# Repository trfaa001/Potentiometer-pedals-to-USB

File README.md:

# DIY USB Game Pedals with Arduino & Logitech G29 Wiring

This project turns **three potentiometers** into fully functional USB game pedals (clutch, brake, accelerator) using an Arduino and the [Arduino Joystick Library](https://github.com/MHeironimus/ArduinoJoystickLibrary).

---

## Features

- **3 Analog Pedals** mapped to USB joystick axes:
  - **Rx** → Pedal 1 (e.g., Clutch)
  - **Ry** → Pedal 2 (e.g., Brake)
  - **Rz** → Pedal 3 (e.g., Accelerator)
- **Gaussian smoothing filter** to reduce noise and jitter
- **Automatic min/max calibration** at startup and during use
- **Compatible with Logitech G29 pedal wiring** (KiCad schematic included)
- **Plug-and-play USB HID device**

---

## Hardware Requirements

- **Arduino Leonardo**, Micro, or any Arduino board with native USB HID support (only tested on Leonardo)  
  *(Uno/Nano will not work without extra firmware flashing)*
- **3x potentiometers** (e.g., from Logitech G29 pedals)
- **Wiring** (Dupont cables or soldered connections)
- *(Optional)* Capacitors for physical low-pass filter.

---

## Wiring

The potentiometers are connected to the Arduino’s analog pins:

| Pedal   | Arduino Pin |
|---------|-------------|
| Pedal 1 | A0          |
| Pedal 2 | A1          |
| Pedal 3 | A2          |

Each potentiometer also connects to **5V** and **GND**.

If using Logitech G29 pedals, refer to the included [**KiCad schematic**](/hardware/kicad/g29pedals/schematic.jpg) for the correct pinout.

---

## Software Setup

1. **Install Arduino IDE**
2. **Install Joystick Library**  
   - Open Arduino IDE → Sketch → Include Library → Manage Libraries  
   - Search for `Joystick` by Matthew Heironimus and install
3. **Select Board**  
   - Tools → Board → Arduino Leonardo (or compatible)
4. **Upload the Code**  
   - Flash the provided `.ino` file to your Arduino

---

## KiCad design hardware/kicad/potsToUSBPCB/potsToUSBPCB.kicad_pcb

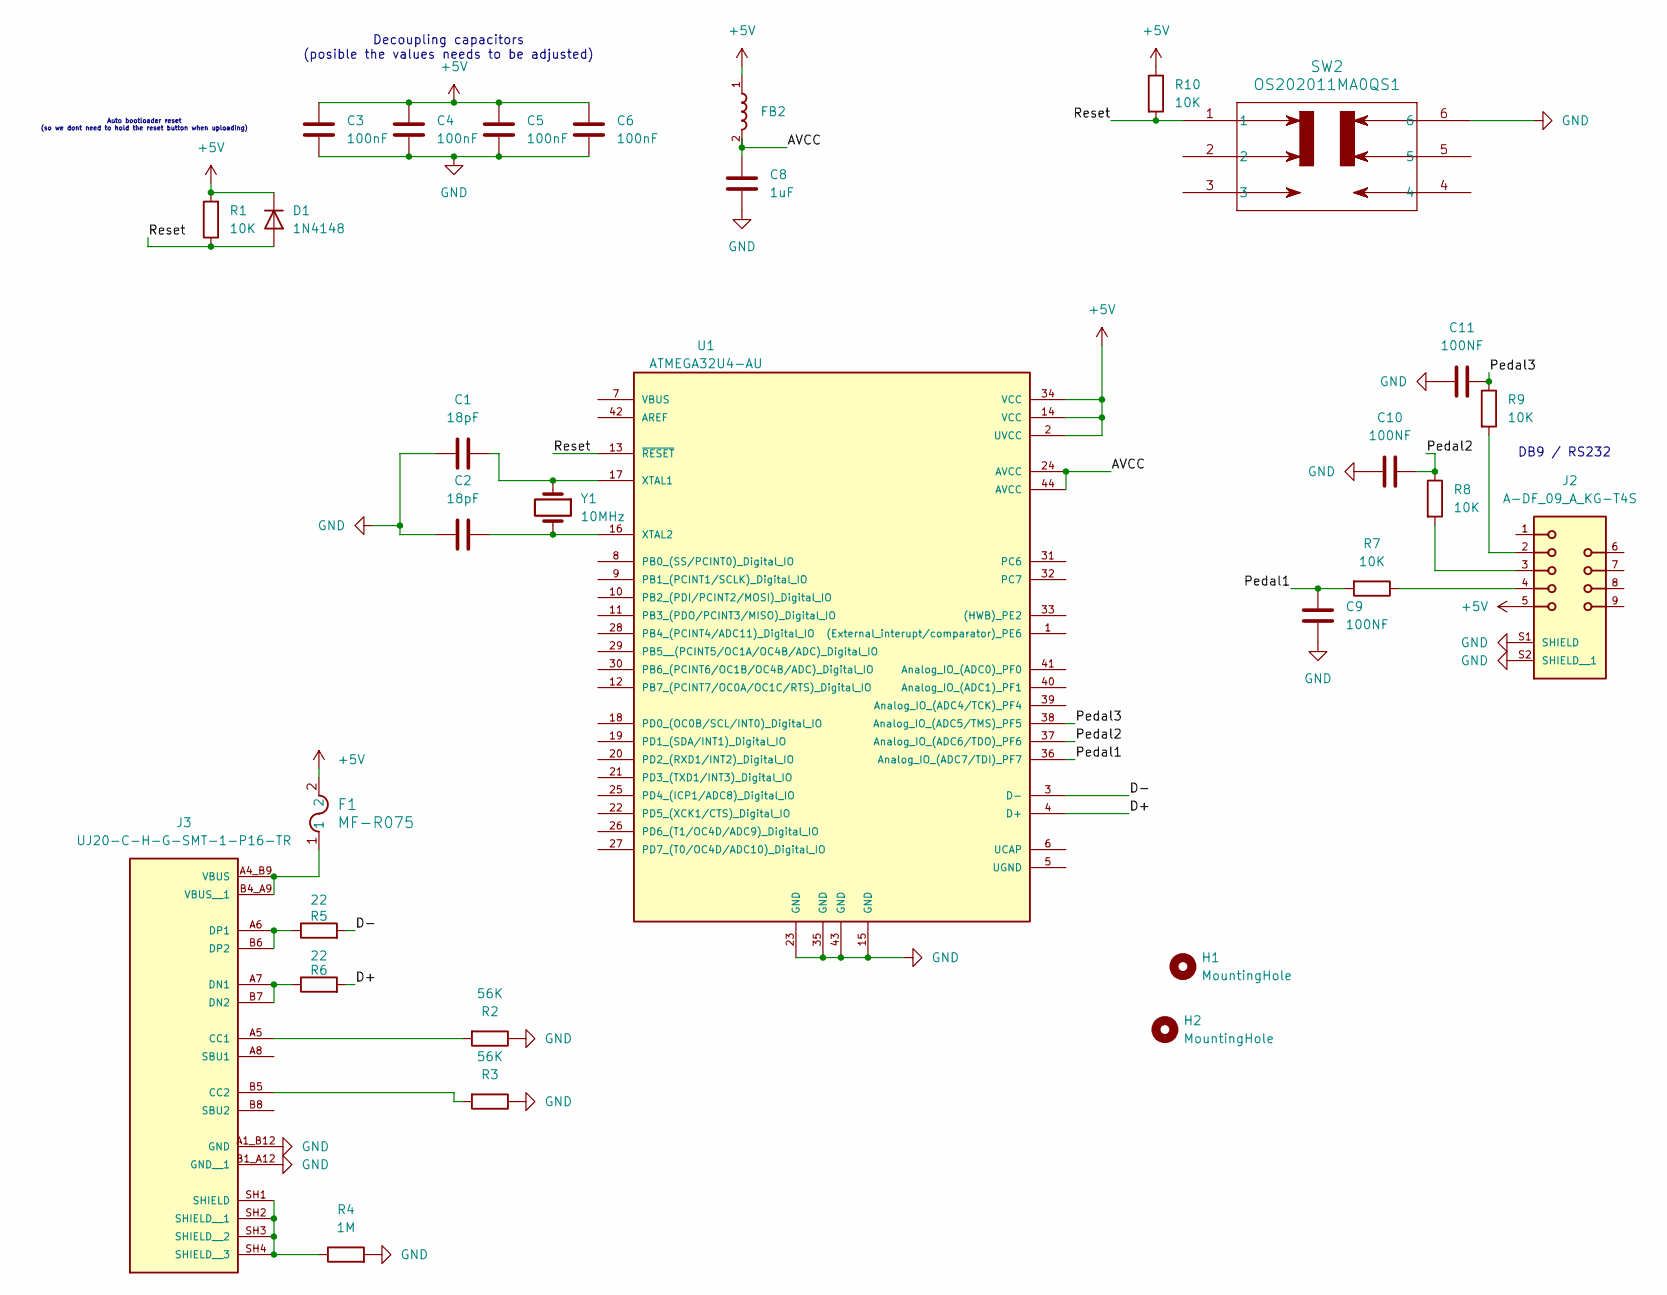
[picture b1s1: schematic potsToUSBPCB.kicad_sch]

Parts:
C1, C2: 18pF; C_Disc_D5.0mm_W2.5mm_P5.00mm
C3, C4, C5, C6: 100nF; C_0805_2012Metric_Pad1.18x1.45mm_HandSolder
C8: 1uF; L_1206_3216Metric_Pad1.42x1.75mm_HandSolder
C9, C10, C11: 100NF; C_0805_2012Metric_Pad1.18x1.45mm_HandSolder
D1: 1N4148; Nexperia_CFP3_SOD-123W
F1: MF-R075; FUS_MF-R075_BRN
FB2: 30R 3A; IND_BOURNS_MH2029; MPN MH2029-300Y
H1, H2: MountingHole; MountingHole_2.2mm_M2
J2: A-DF_09_A_KG-T4S; ASSMANN_A-DF_09_A_KG-T4S; PARTREV 05
J3: UJ20-C-H-G-SMT-1-P16-TR; SAMESKY_UJ20-C-H-G-SMT-1-P16-TR; PARTREV 1.0
R1, R7, R8, R9, R10: 10K; R_1206_3216Metric_Pad1.30x1.75mm_HandSolder
R2, R3: 56K; R_1206_3216Metric_Pad1.30x1.75mm_HandSolder
R4: 1M; R_1206_3216Metric_Pad1.30x1.75mm_HandSolder
R5, R6: 22; R_1206_3216Metric_Pad1.30x1.75mm_HandSolder
SW2: OS202011MA0QS1; SW6_OS202011MA0QS1_CNK
U1: ATMEGA32U4-AU; TQFP-44-1EP_10x10mm_P0.8mm_EP4.5x4.5mm
Y1: 10MHz; XTAL_ABLS2-8.000MHZ-D4Y-T

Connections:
+5V: C3.1, C4.1, C5.1, C6.1, D1.1 (K), F1.2, FB2.1, J2.5, R1.2, R10.1, U1.2 (UVCC), U1.14 (VCC), U1.34 (VCC)
/AVCC: C8.1, FB2.2, U1.24 (AVCC), U1.44 (AVCC)
/D+: R6.2, U1.4 (D+)
/D-: R5.2, U1.3 (D-)
/Pedal1: C9.1, R7.2, U1.36 (Analog_IO_(ADC7/TDI)_PF7)
/Pedal2: C10.1, R8.1, U1.37 (Analog_IO_(ADC6/TDO)_PF6)
/Pedal3: C11.1, R9.1, U1.38 (Analog_IO_(ADC5/TMS)_PF5)
/Reset: D1.2 (A), R1.1, R10.2, SW2.1, U1.13 (~RESET)
GND: C1.2, C2.1, C3.2, C4.2, C5.2, C6.2, C8.2, C9.2, C10.2, C11.2, J2.S1 (SHIELD), J2.S2 (SHIELD__1), J3.A1_B12 (GND), J3.B1_A12 (GND__1), R2.1, R3.1, R4.2, SW2.6, U1.15 (GND), U1.23 (GND), U1.35 (GND), U1.43 (GND)
unnamed: J2.2, R9.2
unnamed: J2.3, R8.2
unnamed: J2.4, R7.1
unnamed: J3.A5 (CC1), R2.2
unnamed: J3.B5 (CC2), R3.2
unnamed: J3.A7 (DN1), J3.B7 (DN2), R6.1
unnamed: J3.A6 (DP1), J3.B6 (DP2), R5.1
unnamed: J3.SH1 (SHIELD), J3.SH2 (SHIELD__1), J3.SH3 (SHIELD__2), J3.SH4 (SHIELD__3), R4.1
unnamed: F1.1, J3.A4_B9 (VBUS), J3.B4_A9 (VBUS__1)
unnamed: C1.1, U1.17 (XTAL1), Y1.1
unnamed: C2.2, U1.16 (XTAL2), Y1.2

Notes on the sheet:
Decoupling capacitors (posible the values needs to be adjusted)
DB9 / RS232
Auto bootloader reset (so we dont need to hold the reset button when uploading)

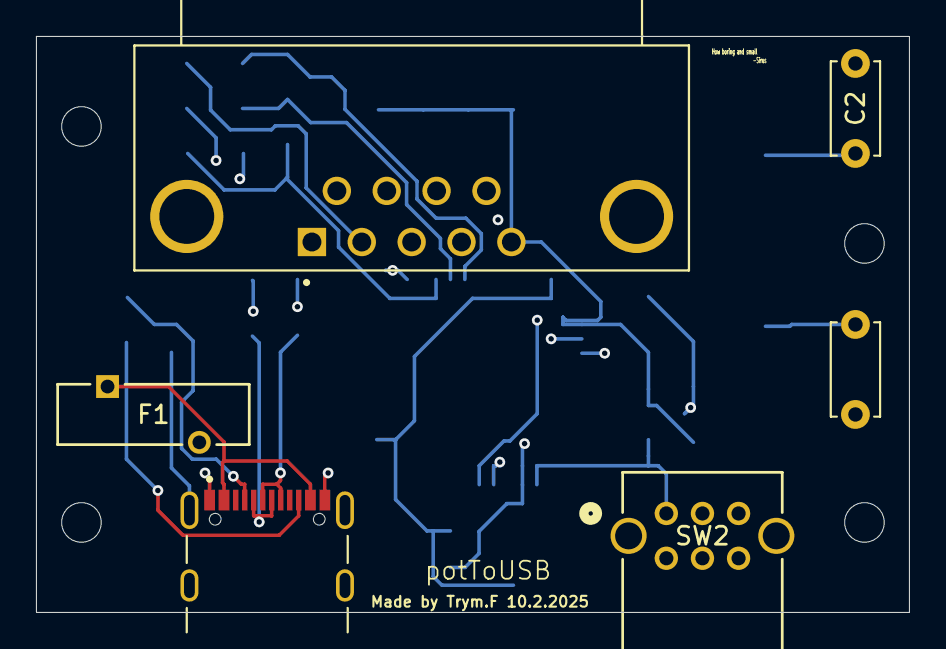
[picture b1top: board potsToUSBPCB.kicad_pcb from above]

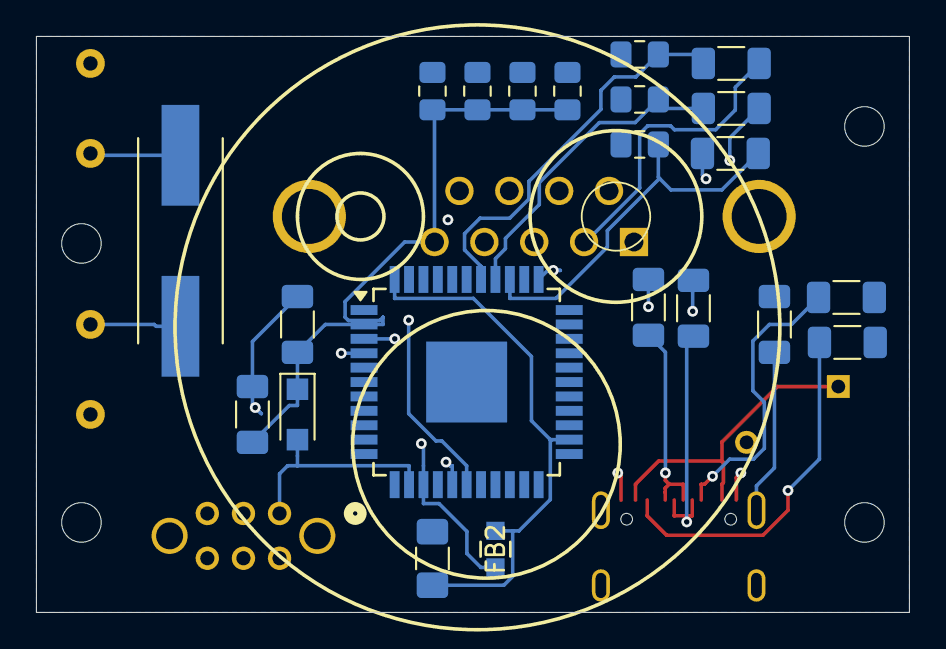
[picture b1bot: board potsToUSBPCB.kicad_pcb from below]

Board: 4 copper layers, 48.5 x 32.0 mm, 32 parts (22 on the bottom side), 20 nets.

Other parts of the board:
H3, H4: MountingHole; MountingHole_2.2mm_M2

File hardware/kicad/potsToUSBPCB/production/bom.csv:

Designator,Footprint,Quantity,Value,LCSC Part #
"C1, C2",C_Disc_D5.0mm_W2.5mm_P5.00mm,2,18pF,
"C10, C11, C3, C4, C5, C6, C9",0805,7,100NF,
C8,1206,1,1uF,
D1,Nexperia_CFP3_SOD-123W,1,1N4148,
F1,FUS_MF-R075_BRN,1,MF-R075,
FB2,IND_BOURNS_MH2029,1,30R 3A,MH2029-300Y
J2,ASSMANN_A-DF_09_A_KG-T4S,1,A-DF_09_A_KG-T4S,
J3,SAMESKY_UJ20-C-H-G-SMT-1-P16-TR,1,UJ20-C-H-G-SMT-1-P16-TR,
"R1, R10, R7, R8, R9",1206,5,10K,
"R2, R3",1206,2,56K,
R4,1206,1,1M,
"R5, R6",1206,2,22,
SW2,SW6_OS202011MA0QS1_CNK,1,OS202011MA0QS1,
U1,TQFP-44-1EP_10x10mm_P0.8mm_EP4.5x4.5mm,1,ATMEGA32U4-AU,
Y1,XTAL_ABLS2-8.000MHZ-D4Y-T,1,10MHz,

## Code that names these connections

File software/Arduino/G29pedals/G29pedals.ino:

#include <Joystick.h>



Joystick_ Joystick(JOYSTICK_DEFAULT_REPORT_ID,JOYSTICK_TYPE_GAMEPAD,
  0, 0,                    // Button Count, Hat Switch Count
  false, false, false,     // No x, Y or Z
  true, true, true,        // Rx, Ry, or Rz
  false, false,            // No rudder or throttle
  false, false, false);    // No accelerator, brake, or steering

// Define IO pins
const int pedal1 = A0;
const int pedal2 = A1;
const int pedal3 = A2;

// Start values for Min and Max values
int pedal1Max = 100;
int pedal1Min = 0;

int pedal2Max = 100;
int pedal2Min = 0;

int pedal3Max = 100;
int pedal3Min = 0;

// Time keeping
unsigned long calibrationStart;
unsigned long timeLastMaxCalibration;

// Variables for logic
unsigned long analogReadings; // Variable to store readings that add up to one big number

int amountOfReadings; // Variable to store the amount of analog readings taken

float dataPedal1[5]; // A collection of the most recent reading from pedal1
float dataPedal2[5]; // A collection of the most recent reading from pedal2
float dataPedal3[5]; // A collection of the most recent reading from pedal3

float kernel[5]; // The kernel for pedal1

float filterOutputPedal1[5]; // The output of the filter from pedal 1
float filterOutputPedal2[5]; // The output of the filter from pedal 2
float filterOutputPedal3[5]; // The output of the filter from pedal 3

float kernelSum = 0; 

// Constant variables for logic
const int amountOfReadingsForMax = 10;
const int millisForMinCalibration = 1000; // The time for taking the average of the "minimum" value of each pedal
const unsigned long timeBetweenMaxCalibration = 5; // The time between checking if there is a new max

const int kernelSize = 5; // Variables for Guassian kernel
const float sigma = 2.0; // Standard deviation

void setup() {
  // Define pin modes
  pinMode(pedal1, INPUT);
  pinMode(pedal2, INPUT);
  pinMode(pedal3, INPUT);

  gaussianKernel(); // Calculates the gaussian kernel

  // Calibrate the minimum of the pedals
  pedal1Min = minCalibration(pedal1);
  pedal2Min = minCalibration(pedal2);
  pedal3Min = minCalibration(pedal3);

  Joystick.begin(); // Begin the joystick library

  setCalibrationForAxis();

  Serial.begin(9600);


}

void loop() {

  // If enough time has passed check if the pedals can reach a higher value
  if ((millis() - timeLastMaxCalibration) > timeBetweenMaxCalibration){
      pedal1Max = maxCalibration(1, pedal1Max);
      pedal2Max = maxCalibration(2, pedal2Max);
      pedal3Max = maxCalibration(3, pedal3Max);
      setCalibrationForAxis();

      timeLastMaxCalibration = millis();
  }

  takeInputs();
  calculateOutput();

  Joystick.setRxAxis(filterOutputPedal1[kernelSize-1]);
  Joystick.setRyAxis(filterOutputPedal2[kernelSize-1]);
  Joystick.setRzAxis(filterOutputPedal3[kernelSize-1]);

}

void setCalibrationForAxis(){
  // Sets the range for the pedals

  Joystick.setRxAxisRange(pedal1Min, pedal1Max);
  Joystick.setRyAxisRange(pedal2Min, pedal2Max);
  Joystick.setRzAxisRange(pedal3Min, pedal3Max);
}

int minCalibration(int analogPin){
  // Reset the variables so the function can be used multiple times
  analogReadings = 0;
  amountOfReadings = 0;
  calibrationStart = millis();

  //Take the average of all the reading in a second and return it (asume the user doesnt touch the pedals the first 3 seconds)
  while ((millis() - calibrationStart) < millisForMinCalibration){
    analogReadings += analogRead(analogPin);
    amountOfReadings += 1;

  }

  return analogReadings / amountOfReadings;
}

int maxCalibration(int pedal, int pedalMax){
  // Reset the variables so the function can be used multiple times
  analogReadings = 0;
  amountOfReadings = amountOfReadingsForMax;

  if (pedal == 1){
    for (int i = 0; i < amountOfReadingsForMax; i++){ //We are only doing 10 readings to save on proccesing time
      analogReadings += filterOutputPedal1[kernelSize-1];
    }
  }
  else if (pedal == 2){
    for (int i = 0; i < amountOfReadingsForMax; i++){ //We are only doing 10 readings to save on proccesing time
      analogReadings += filterOutputPedal2[kernelSize-1];
    }
  }
  else if (pedal == 3){
    for (int i = 0; i < amountOfReadingsForMax; i++){ //We are only doing 10 readings to save on proccesing time
      analogReadings += filterOutputPedal3[kernelSize-1];
    }
  }


  if ((analogReadings / amountOfReadingsForMax) > pedalMax){
    
    return analogReadings / amountOfReadingsForMax;
  }
  else{
    return pedalMax;
  }

    
}

void takeInputs(){
  // Moves the data in the data array one point forward, registering the input and saving the 4 previous ones for later use

  for (int i = 0; i < kernelSize; i++){
    if (i == kernelSize - 1){
      dataPedal1[i] = analogRead(pedal1);
      dataPedal2[i] = analogRead(pedal2);
      dataPedal3[i] = analogRead(pedal3);
    }
    else{ 
      dataPedal1[i] = dataPedal1[i + 1];
      dataPedal2[i] = dataPedal2[i + 1];
      dataPedal3[i] = dataPedal3[i + 1];
    } 
  }
}

//Calculate the gaussian kernel. Could make the code faster by making this only run when sigma is changed
void gaussianKernel() {
  kernelSum = 0;

  for (int i = 0; i < kernelSize; i++) {
    float x = i - kernelSize / 2;
    kernel[i] = exp(-(pow(x, 2)) / (2 * pow(sigma, 2)));
    kernelSum += kernel[i];
  }
  for (int i = 0; i < kernelSize; i++) {
    kernel[i] /= kernelSum;
  }
}

void convolve1d(float* data, float* kernel, float* output, int size) {
  //Convolves

  int halfSize = size / 2;

  for (int i = 0; i < size; i++) {
    float sum = 0.0;
    for (int j = 0; j < size; j++) {
      int dataIndex = i + j - halfSize;
      if (dataIndex >= 0 && dataIndex < size) {
        sum += data[dataIndex] * kernel[j];
      }
    }
    output[i] = sum;
  }
}

void calculateOutput(){
  convolve1d(dataPedal1, kernel, filterOutputPedal1, kernelSize);
  convolve1d(dataPedal2, kernel, filterOutputPedal2, kernelSize);
  convolve1d(dataPedal3, kernel, filterOutputPedal3, kernelSize);
}

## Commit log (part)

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2025-09-14 Initial commit
    First revision of the code and a todo list for future me.
2025-10-01 Intermediate pcb
2025-10-02 Revision 1 (Hopefully the last revision)
2025-10-02 Revision 2 (moved the ports further out)
2025-10-03 Added some things
2026-01-25 First commit of the gui.
2026-02-10 Moved features that will not be finished to a separate folder. The features will not be implemented because of me moving to bigger projects that I am more motivated to finish that covers many of the 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
2026-02-10 Updated readme. Added hyperlink to the schematic.
2026-02-10 Staging moved and new files.
2026-02-10 Updated todo list.
2026-02-10 Updated the readme. Removed emojis, and updated the text.
